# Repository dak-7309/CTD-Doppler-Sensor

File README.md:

# CTD-Doppler-Sensor
Designed and simulated an analog circuit for the transmitter of a Doppler Sensor on LTSpice and fabricated a fully functional PCB using Eagle

Use Eagle and LTSpice to open various files
based on the course project in Circuit Theory and Devices
Under Prof. Shobha Sundar Ram
IIITD

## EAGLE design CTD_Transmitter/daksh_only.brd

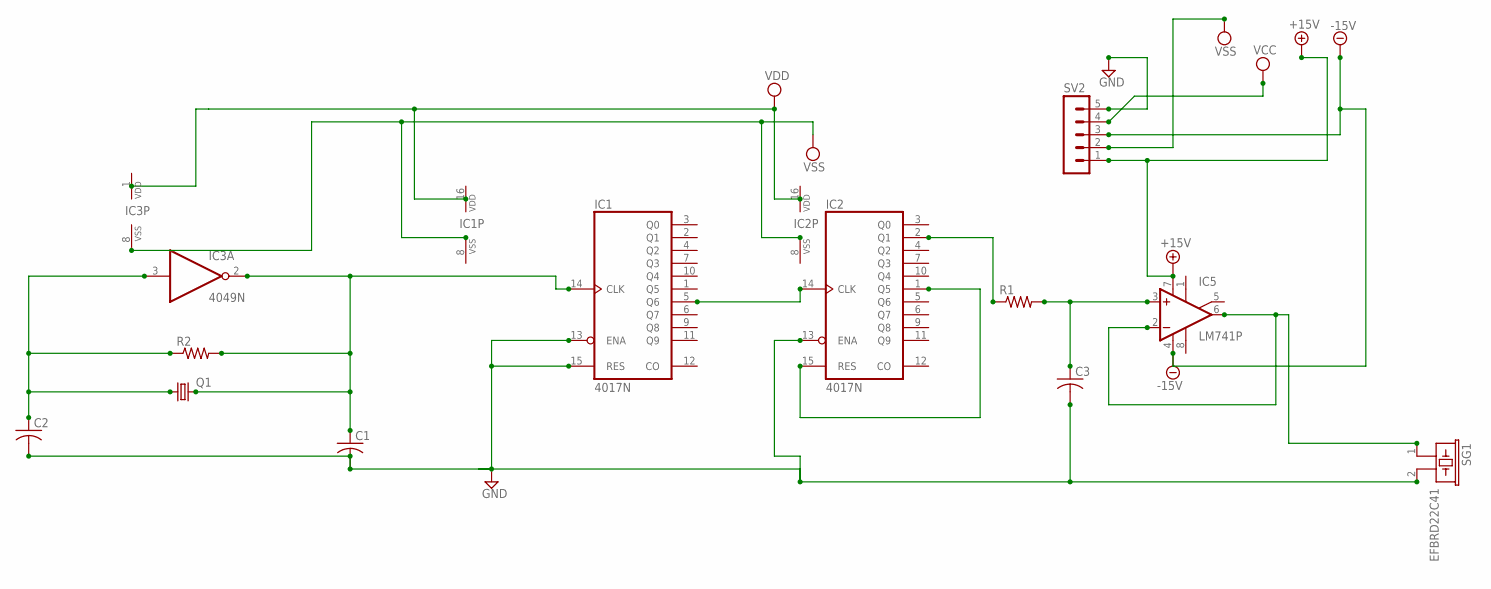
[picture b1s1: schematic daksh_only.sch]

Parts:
C1, C2, C3: C-US025-024X044; C025-024X044
IC1, IC2: 4017N; DIL16
IC3: 4049N; DIL16
IC5: LM741P; DIL08
Q1: CRYSTALHC49U-H; HC49U-H
R1, R2: R-US_0204/5; 0204/5
SG1: EFBRD22C41
SV2: MA05-1

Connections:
+15V: IC5.7 (V+), SV2.1
-15V: IC5.4 (V-), SV2.3
GND: C1.2, C2.2, C3.2, IC1.13 (ENA), IC1.15 (RES), IC2.13 (ENA), SG1.2, SV2.5
unnamed: C2.1, IC3.3 (I), Q1.1, R2.1
unnamed: C1.1, IC1.14 (CLK), IC3.2 (O), Q1.2, R2.2
unnamed: IC1.5 (Q6), IC2.14 (CLK)
unnamed: IC2.2 (Q1), R1.1
unnamed: IC2.1 (Q5), IC2.15 (RES)
unnamed: C3.1, IC5.3 (+IN), R1.2
unnamed: IC5.2 (-IN), IC5.6 (OUT), SG1.1
VCC: SV2.4
VDD: IC1.16 (VDD), IC2.16 (VDD), IC3.1 (VDD)
VSS: IC1.8 (VSS), IC2.8 (VSS), IC3.8 (VSS), SV2.2

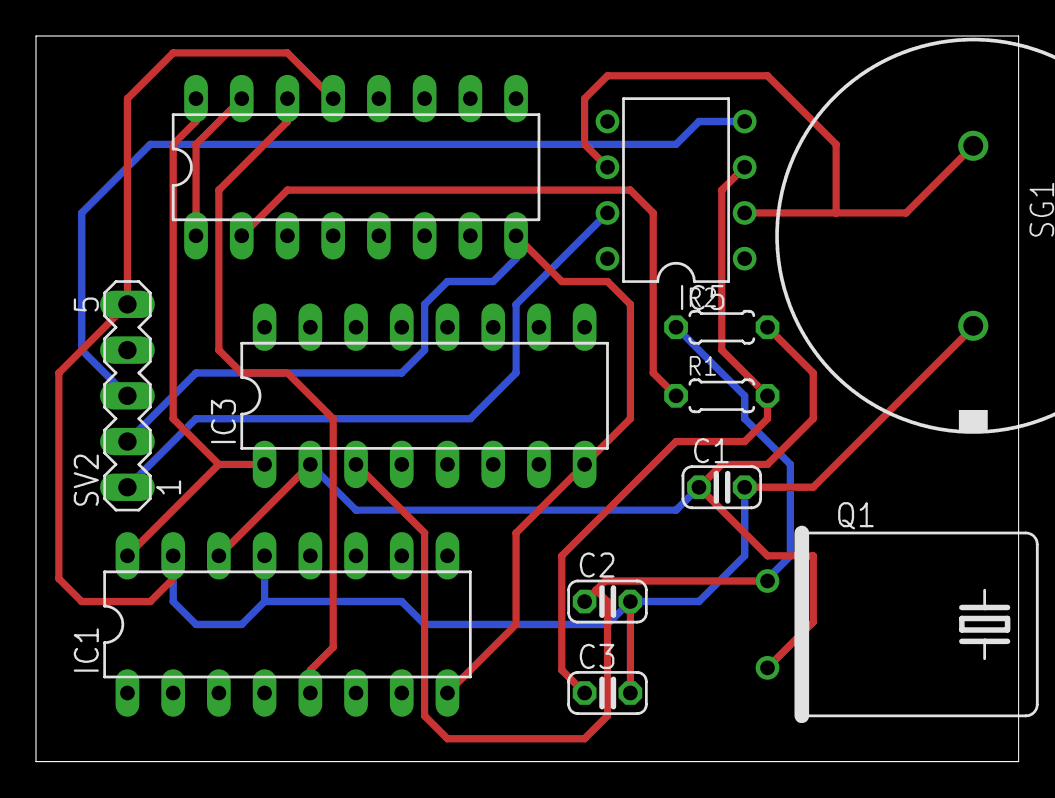
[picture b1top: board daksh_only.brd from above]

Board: 2 copper layers, 54.6 x 40.3 mm, 12 parts (0 on the bottom side), 12 nets.
